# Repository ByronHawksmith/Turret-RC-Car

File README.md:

# Turret-RC-Car

## Attribution and Acknowledgements

- Pan Tilt Mechanism designed by Thingiverse user: eltitomanolo. Available at: https://www.thingiverse.com/thing:2467743
- Automated Gattling Turret designed by Thingiverse user: Canino. Available at: https://www.thingiverse.com/thing:3420083

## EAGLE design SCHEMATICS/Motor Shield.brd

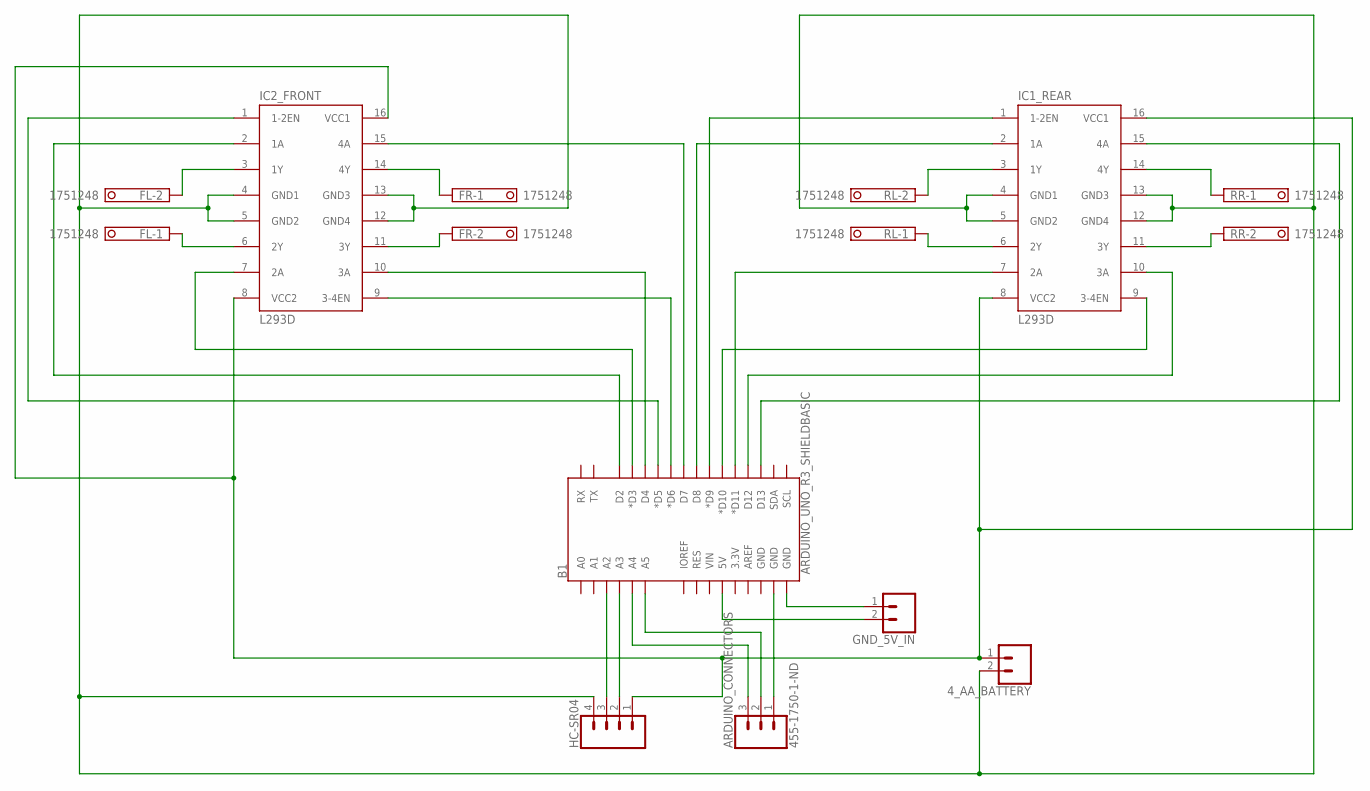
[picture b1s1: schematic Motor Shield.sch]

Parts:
4_AA_BATTERY: CONN_02; 1X02
ARDUINO_CONNECTORS: 455-1750-1-ND; 1X03
B1: ARDUINO_UNO_R3_SHIELDBASIC; UNO_R3_SHIELD
FL: 1751248
FR: 1751248
GND_5V_IN: CONN_02; 1X02
HC-SR04: CONN_04PTH; 1X04
IC1_REAR, IC2_FRONT: L293D; DIL16
RL: 1751248
RR: 1751248

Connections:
D2: B1.D2, IC2_FRONT.2 (1A)
D3: B1.D3 (*D3), IC2_FRONT.7 (2A)
D5: B1.D5 (*D5), IC2_FRONT.1 (1-2EN)
GND: 4_AA_BATTERY.2, HC-SR04.4, IC1_REAR.4 (GND1), IC1_REAR.5 (GND2), IC1_REAR.12 (GND4), IC1_REAR.13 (GND3), IC2_FRONT.4 (GND1), IC2_FRONT.5 (GND2), IC2_FRONT.12 (GND4), IC2_FRONT.13 (GND3)
unnamed: FL.2, IC2_FRONT.3 (1Y)
unnamed: FL.1, IC2_FRONT.6 (2Y)
unnamed: FR.1, IC2_FRONT.14 (4Y)
unnamed: FR.2, IC2_FRONT.11 (3Y)
unnamed: IC1_REAR.3 (1Y), RL.2
unnamed: IC1_REAR.14 (4Y), RR.1
unnamed: IC1_REAR.6 (2Y), RL.1
unnamed: IC1_REAR.11 (3Y), RR.2
unnamed: B1.GND@0 (GND), GND_5V_IN.1
unnamed: B1.D10 (*D10), IC1_REAR.9 (3-4EN)
unnamed: B1.5V, GND_5V_IN.2
unnamed: B1.A2, HC-SR04.3
unnamed: B1.A3, HC-SR04.2
unnamed: B1.D11 (*D11), IC1_REAR.7 (2A)
unnamed: ARDUINO_CONNECTORS.3, B1.A4
unnamed: B1.D9 (*D9), IC1_REAR.1 (1-2EN)
unnamed: B1.D12, IC1_REAR.10 (3A)
unnamed: B1.D13, IC1_REAR.15 (4A)
unnamed: B1.D8, IC1_REAR.2 (1A)
unnamed: B1.D7, IC2_FRONT.15 (4A)
unnamed: B1.D6 (*D6), IC2_FRONT.9 (3-4EN)
unnamed: ARDUINO_CONNECTORS.2, B1.A5
unnamed: B1.D4, IC2_FRONT.10 (3A)
unnamed: ARDUINO_CONNECTORS.1, B1.GND@1 (GND)
VCC: 4_AA_BATTERY.1, HC-SR04.1, IC1_REAR.8 (VCC2), IC1_REAR.16 (VCC1), IC2_FRONT.8 (VCC2), IC2_FRONT.16 (VCC1)

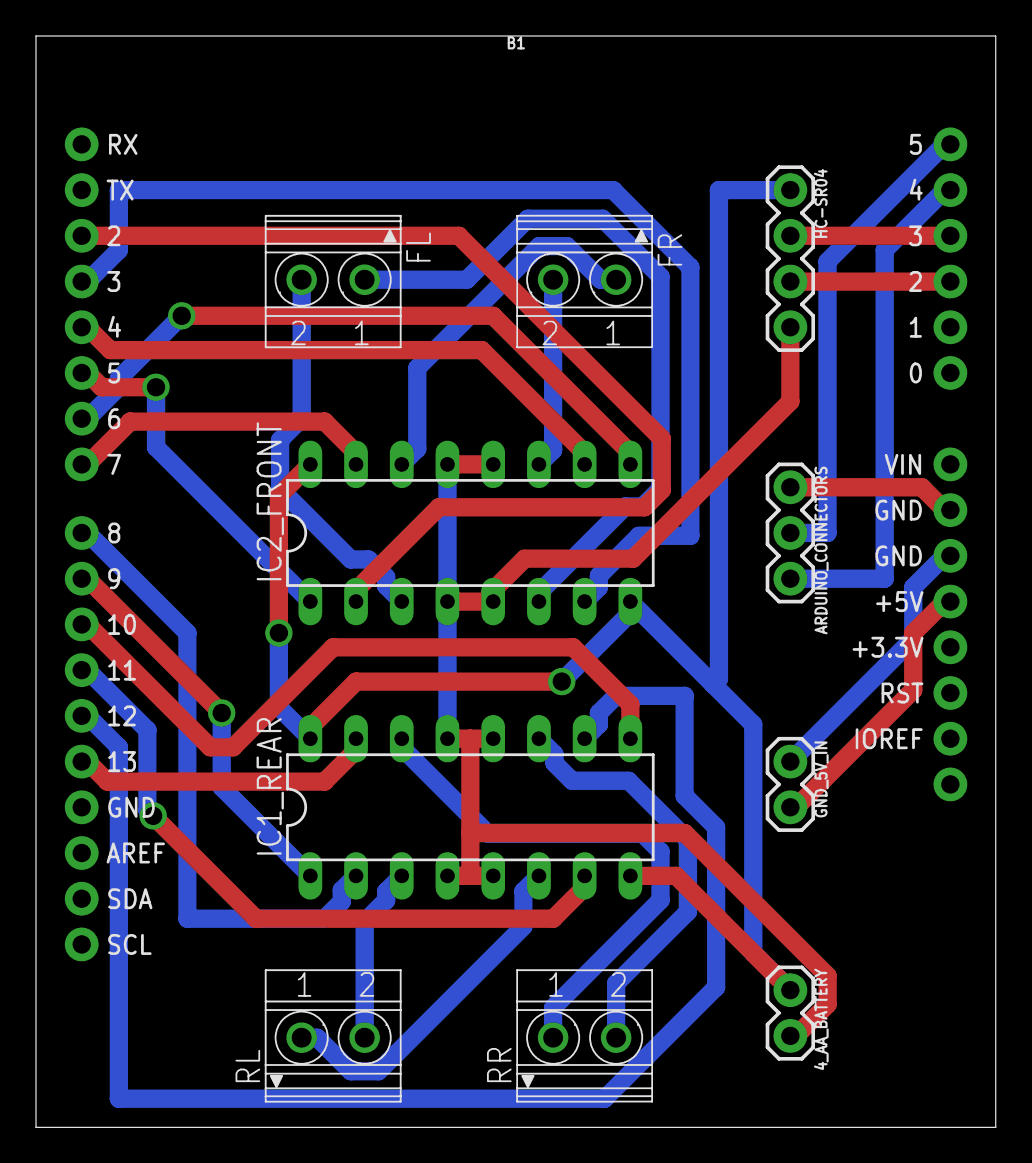
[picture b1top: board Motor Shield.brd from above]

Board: 2 copper layers, 53.3 x 60.6 mm, 11 parts (0 on the bottom side), 29 nets.

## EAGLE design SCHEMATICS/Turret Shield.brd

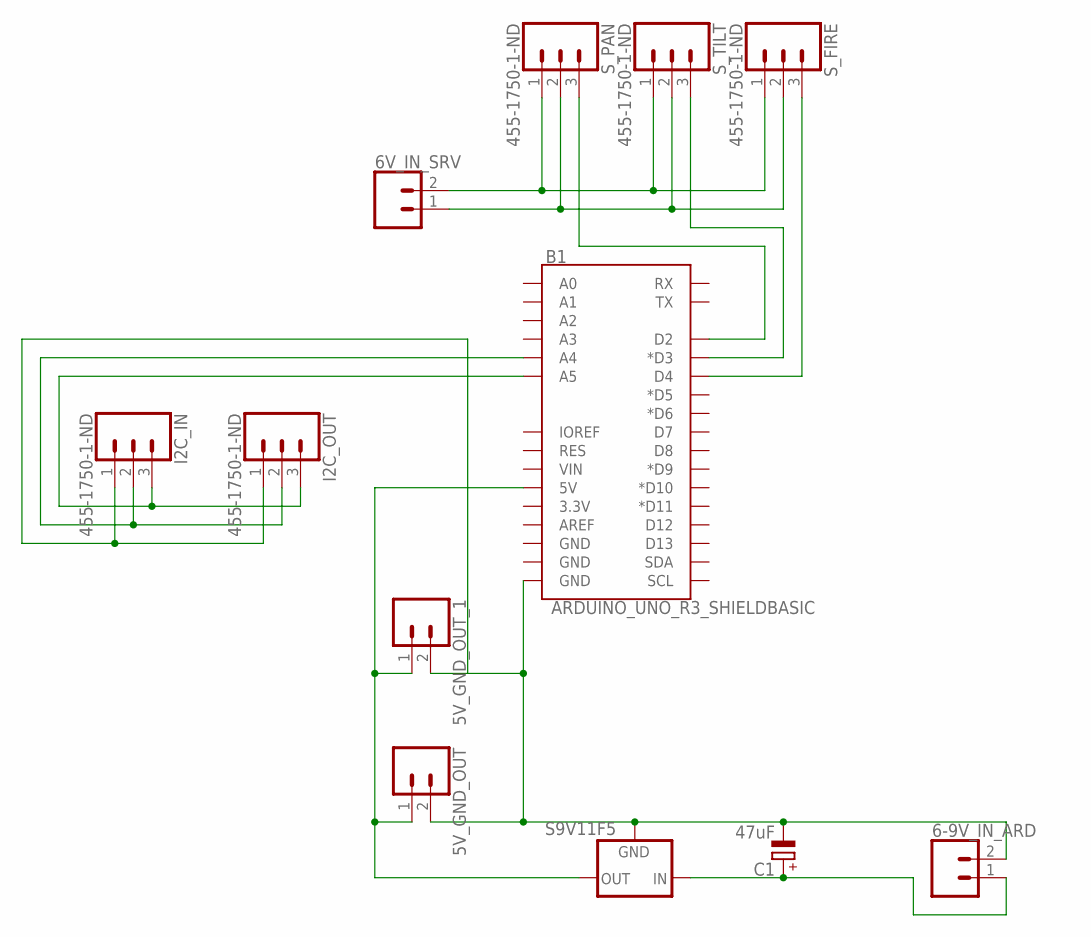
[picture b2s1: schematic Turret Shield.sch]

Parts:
5V_GND_OUT, 5V_GND_OUT_1, 6-9V_IN_ARD, 6V_IN_SRV: CONN_02; 1X02
B1: ARDUINO_UNO_R3_SHIELDBASIC; UNO_R3_SHIELD
C1: 47uF; E2,5-6
I2C_IN, I2C_OUT: 455-1750-1-ND; 1X03
S9V11F5: 78XXS
S_FIRE: 455-1750-1-ND; 1X03
S_PAN: 455-1750-1-ND; 1X03
S_TILT: 455-1750-1-ND; 1X03

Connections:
unnamed: 6V_IN_SRV.1, S_FIRE.2, S_PAN.2, S_TILT.2
unnamed: B1.D3 (*D3), S_TILT.3
unnamed: B1.D2, S_PAN.3
unnamed: 6V_IN_SRV.2, S_FIRE.1, S_PAN.1, S_TILT.1
unnamed: B1.D4, S_FIRE.3
unnamed: 5V_GND_OUT.2, 5V_GND_OUT_1.2, 6-9V_IN_ARD.2, B1.GND@0 (GND), C1.-, I2C_IN.1, I2C_OUT.1, S9V11F5.GND
unnamed: 5V_GND_OUT.1, 5V_GND_OUT_1.1, B1.5V, S9V11F5.OUT
unnamed: 6-9V_IN_ARD.1, C1.+, S9V11F5.IN
unnamed: B1.A5, I2C_IN.3, I2C_OUT.3
unnamed: B1.A4, I2C_IN.2, I2C_OUT.2

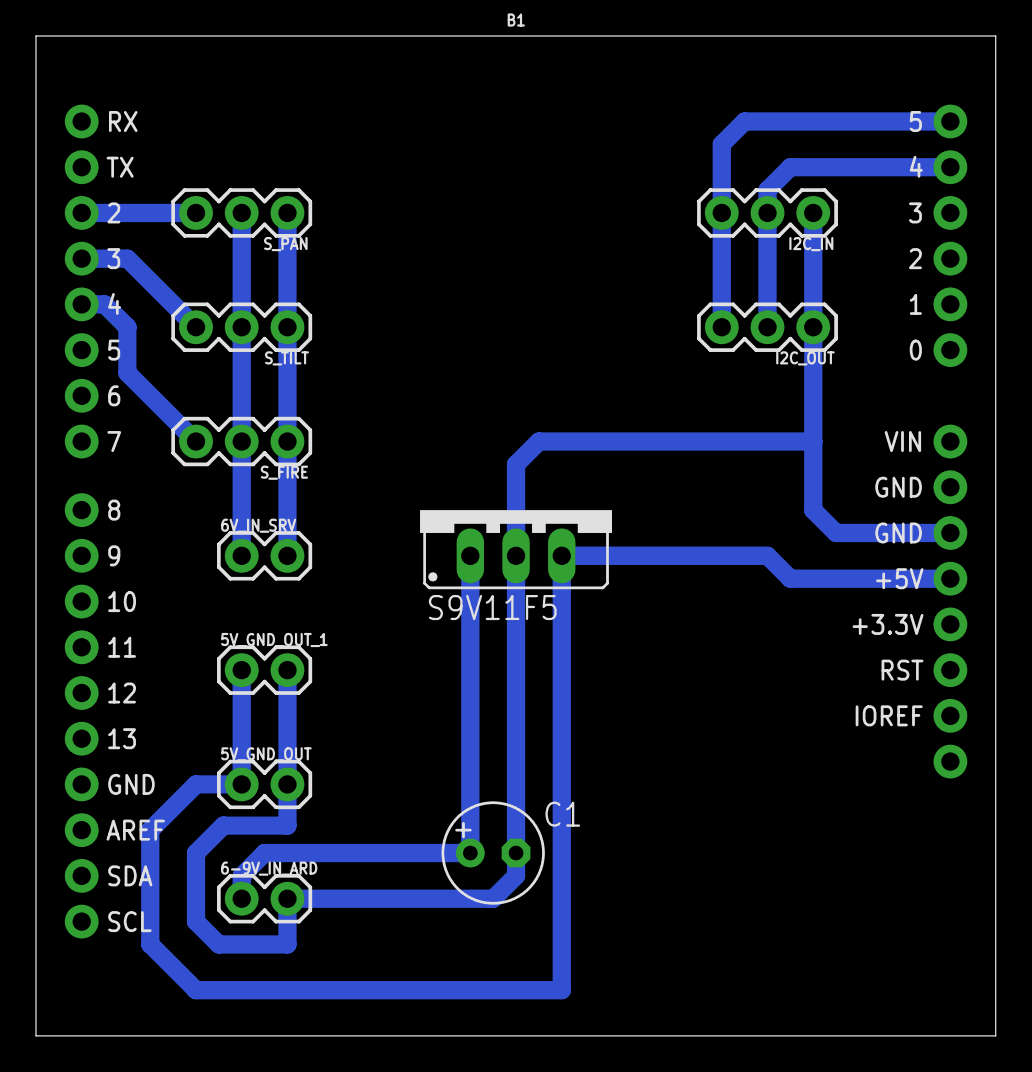
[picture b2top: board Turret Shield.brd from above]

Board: 2 copper layers, 53.3 x 55.5 mm, 12 parts (0 on the bottom side), 10 nets.

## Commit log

2021-04-16 Add additional code to test other L293D
2021-05-10 Add in Wire I2C code.
2021-05-10 Remove comments
2021-05-10 Working code for car broom broom
2021-05-10 Get I2C Working, One Master, Multiple Slaves
2021-05-10 Get Pan and Tilt Servos working with I2C and PS4 Controller
2021-05-10 Get the worlds most terrible 'continuous rotation' servo (which spins the wrong way) working
2021-05-26 Add Schematics

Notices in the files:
parts and their libraries:
SparkFun-Connectors: Licensing: Creative Commons ShareAlike 4.0 International - https://creativecommons.org/licenses/by-sa/4.0
